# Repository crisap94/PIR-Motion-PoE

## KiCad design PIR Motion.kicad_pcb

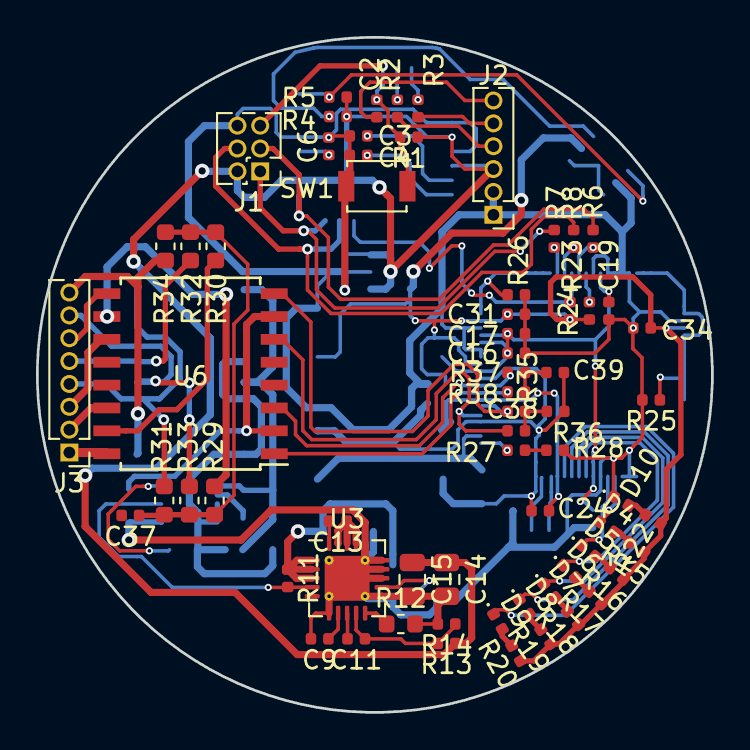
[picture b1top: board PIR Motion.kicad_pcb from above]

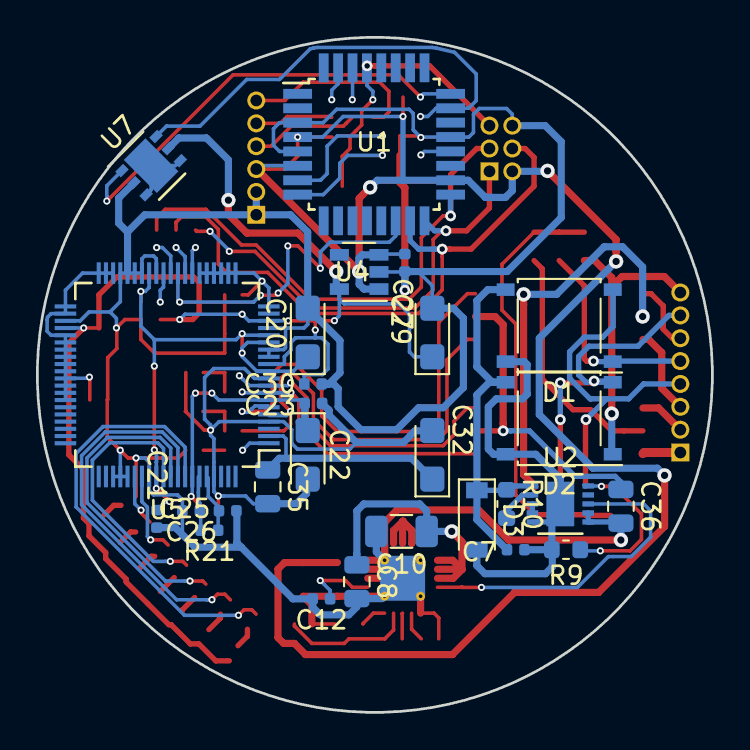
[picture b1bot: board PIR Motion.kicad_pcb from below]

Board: 2 copper layers, 37.5 x 37.5 mm, 93 parts (27 on the bottom side), 76 nets.

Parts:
C2, C6, C7, C16, C17, C19, C21, C23, C24, C27, C30, C31, C34, C37, C38, C39: 0.1uF; C_0402_1005Metric
C3, C4: 22pF; C_0402_1005Metric
C8, C14, C15: 22uF; C_0805_2012Metric
C9: 0.018uF; C_0402_1005Metric
C10: 2.2uF; C_1206_3216Metric
C11: 1pF; C_0402_1005Metric
C12, C13: 2.2uF; C_0402_1005Metric
C20, C22, C29, C32: 10uF/16v; CP_EIA-3216-18_Kemet-A
C25, C26: 13pF; C_0402_1005Metric
C35, C36: 100pF; C_0805_2012Metric
D1, D2: MB6S; Diode_Bridge_Diotec_ABS
D3: 58V; D_SOD-123
D4, D5, D6, D7, D8, D9: LED; LED_0402_1005Metric
D10: pwr; LED_0402_1005Metric
J1: AVR-ISP-6; PinHeader_2x03_P1.27mm_Vertical
J2: FTDI; PinHeader_1x06_P1.27mm_Vertical
J3: RJ45; PinHeader_1x08_P1.27mm_Vertical
R1, R2, R3, R6, R7, R8: 1k; R_0402_1005Metric
R4, R5, R23, R24, R25, R26: 4k7; R_0402_1005Metric
R9: 619; R_0603_1608Metric
R10: 24k9; R_0603_1608Metric
R11: 3M3; R_0402_1005Metric
R12: 68K; R_0603_1608Metric
R13: 154K; R_0402_1005Metric
R14: 34K; R_0402_1005Metric
R15, R16, R17, R18, R19, R20, R22: 470; R_0402_1005Metric
R21: 1M; R_0402_1005Metric
R27: 12k; R_0402_1005Metric
R28: 300; R_0402_1005Metric
R29, R30, R31, R32, R33, R34: 75; R_0603_1608Metric
R35, R36, R37, R38: 49.9; R_0402_1005Metric
SW1: Reset; SW_SPST_B3U-1000P
U1: ATmega328P-AU; TQFP-32_7x7mm_P0.8mm
U2: MAX5969BETB+; DFN-10-1EP_3x3mm_P0.5mm_EP1.55x2.48mm
U3: MAX17503ATP+T; QFN-20-1EP_4x4mm_P0.5mm_EP2.5x2.5mm_ThermalVias
U4: RT9013-XXX; SOT-23-5
U5: W5100; LQFP-80_10x10mm_P0.4mm
U6: RJ45-1-Port-Transformer; SOIC-16W_7.5x10.3mm_P1.27mm
U7: SHT21D; DFN-6-1EP_3x3mm_P0.95mm_EP1.7x2.6mm

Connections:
+3V3: C29.1, C30.1, C31.1, C34.1, R15.1, R16.1, R17.1, R18.1, R19.1, R20.1, R22.2, R23.1, R24.1, U4.5, U5.12, U5.18, U5.44, U7.5
/Atmega/5V: C14.1, C15.1, C27.1, J1.2, J2.3, R1.1, R4.2, R5.2, R13.1, U1.4, U1.6, U1.18, U4.1, U4.3
/Atmega/D11: J1.4, R8.2, U1.15
/Atmega/D12: J1.1, R7.2, U1.16
/Atmega/D13: J1.3, R6.2, U1.17
/Atmega/MISO: R7.1, U5.27
/Atmega/MOSI: R8.1, U5.28
/Atmega/RESET: C2.2, J1.5, R1.2, SW1.2, U1.29
/Atmega/RX: J2.4, R2.1
/Atmega/SCK: R6.1, U5.30
/Atmega/SCL: R4.1, U1.23, U7.6
/Atmega/SDA: R5.1, U1.24, U7.1
/Atmega/TX: J2.5, R3.1
/Atmega/XTAL1: C3.2, U1.7
/Atmega/XTAL2: C4.2, U1.8
/Buck Converter/EN-UVLO: R11.2, U2.8, U3.4
/Buck Converter/FEEDBACK: C11.1, R13.2, R14.1, U3.9
/Buck Converter/VCC: C7.1, D1.3, D2.3, D3.1, R10.1, U2.1
/Ethernet Controller/1V8A: C22.1, C23.1, C24.1, U5.7, U5.74
/Ethernet Controller/1V8D: C16.1, C17.1, C19.1, C20.1, C21.1, U5.11, U5.15, U5.16, U5.33, U5.69
/Ethernet Controller/3V3A: C32.1, C35.1, U5.2
/Ethernet Controller/COL_LED: D7.1, U5.71
/Ethernet Controller/FDX_LED: D6.1, U5.70
/Ethernet Controller/LINK_LED: D4.1, U5.66
/Ethernet Controller/RD+: R36.2, U5.5, U6.6
/Ethernet Controller/RD-: R35.2, U5.6, U6.8
/Ethernet Controller/RX_LED: D8.1, U5.72
/Ethernet Controller/SCS: R23.2, U1.14, U5.29
/Ethernet Controller/SPD_LED: D5.1, U5.67
/Ethernet Controller/TD-: R37.2, U5.9, U6.3
/Ethernet Controller/TX+: R38.2, U5.8, U6.1
/Ethernet Controller/TX_LED: D9.1, U5.73
/Ethernet Controller/XTLN: C26.1, R21.2, U5.75
/Ethernet Controller/XTLP: C25.1, R21.1, U5.76
/PoE PD/VC1: D1.2, J3.4, R31.1
/PoE PD/VC2: D1.1, J3.5, R32.1
/PoE PD/VC3: D2.2, J3.7, R33.1
/PoE PD/VC4: D2.1, J3.8, R34.1
Earth: C3.1, C4.1, C6.2, C8.2, C9.2, C10.2, C12.2, C14.2, C15.2, C16.2, C17.2, C19.2, C20.2, C21.2, C25.2, C26.2, C27.2, C29.2, C30.2, C31.2, C34.2, C36.2, D10.1, J1.6, J2.1, J2.2, R12.2, R14.2, R25.2, R26.2, R28.2, SW1.1, U1.3, U1.5, U1.21, U2.6, U2.7, U3.6, U3.11, U3.13, U3.14, U3.15, U3.16, U3.21, U4.2, U5.13, U5.14, U5.17, U5.32, U5.34, U5.35, U5.36, U5.37, U5.43, U5.63, U5.64, U5.65, U5.68, U7.2
GNDA: C22.2, C23.2, C24.2, C32.2, C35.2, C38.1, C39.1, U5.4, U5.10, U5.77
unnamed: C2.1, J2.6
unnamed: C6.1, U1.20
unnamed: C7.2, D1.4, D2.4, D3.2, R9.2, U2.5, U2.11
unnamed: C9.1, U3.7
unnamed: C8.1, C10.1, R11.1, U3.1, U3.2, U3.3
unnamed: C11.2, U3.8
unnamed: C12.1, U3.12
unnamed: C13.1, U3.17, U3.18, U3.19
unnamed: C13.2, U3.20
unnamed: C36.1, U6.2, U6.7
unnamed: C37.1, R29.2, R30.2, R31.2, R32.2, R33.2, R34.2
unnamed: C38.2, R35.1, R36.1
unnamed: C39.2, R37.1, R38.1
unnamed: D4.2, R15.2
unnamed: D5.2, R16.2
unnamed: D6.2, R17.2
unnamed: D7.2, R18.2
unnamed: D8.2, R19.2
unnamed: D9.2, R20.2
unnamed: D10.2, R22.1
unnamed: J3.1, U6.16
unnamed: J3.2, U6.14
unnamed: J3.3, U6.11
unnamed: J3.6, U6.9
unnamed: R2.2, U1.30
unnamed: R3.2, U1.31
unnamed: R9.1, U2.10
unnamed: R10.2, U2.2
unnamed: R12.1, U3.10
unnamed: R24.2, U5.31
unnamed: R25.1, U5.38, U5.39, U5.40, U5.41, U5.42, U5.45, U5.46, U5.47, U5.48, U5.49, U5.50, U5.51, U5.52, U5.53, U5.54
unnamed: R26.1, U5.19, U5.20, U5.21, U5.22, U5.23, U5.24, U5.25, U5.26
unnamed: R27.1, U5.1
unnamed: R27.2, R28.1
unnamed: R29.1, U6.10
unnamed: R30.1, U6.15
